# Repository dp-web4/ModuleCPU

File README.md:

# ModuleCPU

**ModBatt Battery Management System - Module Controller**

## Overview

ModuleCPU is the middle-tier controller in ModBatt's hierarchical battery management system, coordinating up to 128 individual CellCPUs while reporting aggregated data to the Pack Controller. It demonstrates how distributed intelligence principles can be applied to embedded battery management at the module scale.

**Implementation Status**: ✅ **Production-ready** - Complete firmware with CAN bus communication, VUART cell management, and hierarchical coordination

### Quick Facts

- **Target Platform**: ATmega64M1 microcontroller (8-bit AVR with CAN)
- **Manages**: Up to 128 CellCPUs via Virtual UART daisy-chain
- **Uplink**: CAN 2.0B bus to Pack Controller (250kbps)
- **Features**: Dual-phase operation, RTC timestamping, robust error handling
- **Role**: Middle management - aggregates cell data, coordinates without micromanaging

## Web4 Ecosystem Context

ModuleCPU can be viewed as a practical demonstration of trust-native architecture patterns applied to embedded battery management:

**Philosophical Framework**: [Synchronism](https://github.com/dp-web4/Synchronism) - Patterns of scale-based coordination and distributed intelligence
**Technical Standard**: [Web4](https://github.com/dp-web4/web4) - Concepts like unforgeable identity and witnessed relationships
**Implementation**: [CellCPU](https://github.com/dp-web4/CellCPU) → **ModuleCPU** (this) → [Pack-Controller](https://github.com/dp-web4/Pack-Controller-EEPROM)

### Design Patterns

ModuleCPU's architecture reflects several patterns that align with Web4 and Synchronism concepts:

- **Identity**: Module serial number framework ready for LCT binding
- **Interface Boundaries**: Well-defined information hiding between layers (CAN upward, VUART downward)
- **Relationship Tracking**: Module maintains awareness of Pack Controller and 94 cells
- **Hierarchical Coordination**: Operates autonomously within constraints from Pack
- **Information Aggregation**: Compresses 188 cell data points into module-level summaries
- **Emergent Intelligence**: System-level balancing from distributed local decisions

See [WEB4_INTEGRATION.md](WEB4_INTEGRATION.md) for how Web4 concepts map to embedded design.
See [SYNCHRONISM_PRINCIPLES.md](SYNCHRONISM_PRINCIPLES.md) for architectural patterns and philosophy.

### Ecosystem Links

- [Synchronism Whitepaper](https://github.com/dp-web4/Synchronism) - Theoretical framework
- [Web4 Standard](https://github.com/dp-web4/web4) - Trust-native architecture concepts
- [ModBatt Web4 Examples](https://github.com/dp-web4/web4/blob/main/docs/modbatt_implementation_examples.md) - Implementation walkthroughs

**This demonstrates how concepts from distributed intelligence theory can inform practical embedded system design.**

---

## Key Features

### 🔋 Cell Management
- **Capacity**: Manages up to 128 CellCPUs in daisy-chain topology
- **Communication**: Virtual UART at 20kbps for cell polling
- **Monitoring**: Aggregates temperature, voltage, and status from all cells
- **Coordination**: Enables balancing, tracks cell health, detects faults

### 📡 Pack Communication
- **Protocol**: CAN 2.0B extended frames with module ID addressing
- **Registration**: Dynamic ID assignment (1-31) from Pack Controller
- **Reporting**: Module-level status, aggregated cell data, error conditions
- **Commands**: State changes, balancing control, time synchronization

### ⚙️ Core Capabilities
- **Dual-Phase Operation**: Separate read/write phases for data integrity
- **RTC Support**: Real-time clock for timestamping
- **Error Handling**: Robust timeout and recovery mechanisms
- **State Management**: OFF/STANDBY/ACTIVE/BALANCE states with safety checks

### 🎯 Performance
- **Memory**: 64KB Flash, 4KB SRAM
- **Response Time**: <50ms for full cell poll cycle (94 cells)
- **CAN Reliability**: Timeout recovery, bus-off handling, error counting
- **Cell Tracking**: Bitmap and statistics for each cell position

## Protocol Synchronization

**Important**: ModuleCPU uses shared CAN protocol definitions maintained in the Pack-Controller-EEPROM repository.

**Authoritative Source**: [Pack-Controller-EEPROM/protocols/](https://github.com/dp-web4/Pack-Controller-EEPROM/tree/main/protocols)
**Local Copy**: `protocols/` (synchronized via `scripts/sync_protocols.sh`)

To update protocols after changes in Pack-Controller:
```bash
./scripts/sync_protocols.sh
# Review changes, test build, commit
```

See `protocols/SYNC_NOTICE.md` for synchronization procedure and versioning.

## System Integration

### ModBatt Architecture

```
Vehicle Control Unit (VCU)
    ↓ CAN Bus
Pack Controller (STM32WB55)
    ↓ CAN Bus (250kbps, extended frames)
ModuleCPU (ATmega64M1) ←─→ 128 × CellCPU (ATtiny45)
    ↓ Virtual UART (20kbps)     ↓
Battery Module             Li-ion Cells
```

### Information Flow

**Upward (Aggregation)**:
```
94 cells × (temp + voltage) = 188 data points
    ↓ (Module aggregates)
Module summary: avg/min/max temps, voltage spread, status bitmap
    ↓ (via CAN)
Pack Controller receives compressed module-level view
```

**Downward (Commands)**:
```
Pack: "Modules enter BALANCE state" (broadcast or targeted)
    ↓ (Module interprets)
Module: Polls cells, coordinates balancing based on voltages
    ↓ (Cells execute)
Cells: Activate balancing FETs based on local decisions
```

## Build Environment

**Important**: This project runs in WSL but uses Windows-based build tools.

- **IDE**: Atmel Studio 7.0+ (Windows)
- **Build**: Must compile in Windows environment
- **WSL**: Used for version control and documentation only
- **Focus**: Code correctness and architecture

See [CLAUDE.md](CLAUDE.md) for development context and recent improvements.

## Recent Enhancements

### Protocol Dependency Resolution (October 2025)
- ✅ Added local `protocols/` directory with sync script
- ✅ Resolved Pack-Controller build dependency
- ✅ ModuleCPU now builds standalone

### CAN Reliability Improvements (September 2025)
- ✅ TX timeout mechanism with backup polling
- ✅ Bus-off recovery with health monitoring
- ✅ Adaptive backoff for persistent errors
- ✅ Diagnostic counters for error tracking

### VUART Edge Detection Fix (September 2025)
- ✅ Rising edge detection for level-shifted signals
- ✅ Improved temperature data reliability
- ✅ Better daisy-chain communication

See [CLAUDE.md](CLAUDE.md) for complete development history and technical details.

## Contributing

See [CONTRIBUTING.md](CONTRIBUTING.md) for development workflow, coding standards, and pull request guidelines.

## License and Patents

### Software License

This software is licensed under the **GNU Affero General Public License v3.0 or later** (AGPL-3.0-or-later).

See [LICENSE](LICENSE) for full license text.
See [LICENSE_SUMMARY.md](LICENSE_SUMMARY.md) for software vs. hardware licensing details.

### Patents

Protected by US Patents:
- **11,469,470**: Hierarchical battery management architecture
- **11,380,942**: Distributed cell controller system
- **11,575,270**: Related pack control systems

**Patent Grant**: Limited patent grant for software use under AGPL-3.0. See [PATENTS.md](PATENTS.md).

**Hardware Licensing**: Separate from software. See `docs/legal/ModBatt_Product_License.pdf`.

### Copyright

© 2023-2025 Modular Battery Technologies, Inc.

**Open Source Release**: October 2025 - Part of the Web4 trust-native ecosystem demonstration.

---

## Related Projects

This repository can be viewed as demonstrating patterns of distributed trust and verifiable provenance in embedded systems.

**Related**: [Web4](https://github.com/dp-web4/web4) (trust architecture) • [Synchronism](https://github.com/dp-web4/Synchronism) (conceptual framing)

---

**Note**: This firmware demonstrates hierarchical coordination patterns in embedded systems. Whether viewed through the lens of Web4/Synchronism concepts or simply as sound battery management architecture, the design patterns are production-tested and functional.

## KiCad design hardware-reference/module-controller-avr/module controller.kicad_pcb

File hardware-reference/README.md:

# ModuleCPU Hardware Reference Designs

**Status**: Reference designs for educational and non-commercial use
**Patent Coverage**: Protected by US Patent 11,469,470 (Hierarchical battery management architecture)
**Last Updated**: October 2025

---

## Overview

This directory contains reference hardware designs for implementing the ModuleCPU concept - a module-level coordinator managing up to 94 autonomous cell controllers. These designs demonstrate one possible hardware implementation of the patented hierarchical battery management architecture.

**Contents**:
- KiCad schematics and PCB layouts
- Bill of Materials (BOM)
- Manufacturing files

---

## Patent Coverage

These hardware designs implement concepts covered by multiple patents in the ModBatt patent portfolio:

### Complete Patent List

**Modular Battery Technologies, Inc. Patent Portfolio**:

1. **US 11,380,942** (PCT/US21/50518) - *High Voltage Battery Module with Series Connected Cells and Internal Relays*
   - Filed: November 2, 2020 | Issued: July 5, 2022
   - Module with series connected cells and relays

2. **US 11,469,470** (PCT/US21/53798) - *Battery Module with Series Connected Cells, Internal Relays and Internal Battery Management System*
   - Filed: January 4, 2021 | Issued: October 11, 2022
   - Cell monitoring/conditioning circuit, PCBAs, methods

3. **US 11,563,241** - *Apparatus and Methods for Removable Battery Module with Internal Relay and Internal Controller*
   - Filed: February 10, 2021 | Issued: December 14, 2022
   - Authentication methods and circuits

4. **US 11,575,270** (PCT/US21/55047) - *Battery Module with Series Connected Cells, Internal Relays and Internal Battery Management System*
   - Filed: February 22, 2021 (CIP) | Issued: February 7, 2023
   - AC coupled comms and methods

5. **US 11,699,817** (PCT/US21/54434) - *Apparatus and Methods for Removable Battery Module with Internal Relay and Internal Controller*
   - Filed: March 31, 2021 | Issued: July 11, 2023
   - System, pack and module controllers, blockchain

6. **US 11,477,027** (PCT/US21/55813) - *Apparatus and Methods for Management of Controlled Objects*
   - Filed: May 11, 2021 | Issued: October 18, 2022
   - Multi-domain management of controlled objects, LCT/blockchain

7. **US 11,936,008** (PCT/US21/60860) - *Electrical Power System with Removable Battery Modules*
   - Filed: November 17, 2021 | Issued: March 19, 2024
   - Dissimilar modules in parallel

8. **US 12,278,913** (PCT/US22/24797) - *Apparatus and Methods for Management of Controlled Objects*
   - Filed: March 31, 2022 | Issued: April 15, 2025
   - Linking of identifiable records

9. **US 11,876,250** (PCT/US22/xxx) - *High Voltage Battery Module with Series Connected Cells and Internal Relays*
   - Filed: May 31, 2022 | Issued: January 16, 2024
   - Dissimilar relays, PLC control bus, linear and PWM modes

10. **US 12,046,722** - *Electrical Power System with Removable Battery Modules*
    - Filed: December 12, 2022 | Issued: July 23, 2024
    - Vehicle and stationary installations having a power system, energizing a bus

11. **US 12,405,309** - *Low Cost Battery Cell Monitoring Circuit*
    - Filed: January 3, 2023 | Issued: September 2, 2025
    - Low cost ASIC

12. **US 12,136,739** - *Low Cost Battery Cell Monitoring Circuit*
    - Filed: December 14, 2023 | Issued: November 5, 2024
    - Low cost ASIC methods

13. **US 12,142,737** - *Electrical Power System with Removable Battery Modules*
    - Filed: December 14, 2023 | Issued: November 12, 2024

14. **US 18/935,265** - *High Voltage Battery Module with 1-Phase and 3-Phase AC Output*
    - Filed: November 1, 2024 | Status: Pending

**Assignee**: Modular Battery Technologies, Inc.
**Inventors**: Dennis Palatov, et al.

### Key Patented Concepts in ModuleCPU Hardware

- Module-level coordination of multiple autonomous cell controllers
- Virtual UART aggregation and CAN bus gateway
- Dual-phase operation for data integrity
- Scale-based hierarchical autonomy with information hiding
- RTC timestamping and coordinated data collection
- High voltage module architecture with internal relays
- Module authentication and blockchain integration
- Dissimilar module operation in parallel configurations
- AC-coupled communication methods

---

## License and Usage Terms

### Software License
The **ModuleCPU firmware** (parent directory) is licensed under **AGPL-3.0-or-later** with a patent grant for software use. See `../LICENSE` for details.

### Hardware Reference Designs
These hardware reference designs are provided under the following terms:

#### ✅ Permitted Uses (Non-Commercial Patent Grant)

You MAY use these designs **without a commercial hardware license** for:

1. **Educational Use**: Academic research, teaching, and learning
2. **Personal/Hobby Use**: Individual projects and experimentation
3. **Research & Development**: Prototyping and testing new concepts
4. **Open Source Development**: Contributing to AGPL-licensed software improvements

**Conditions**:
- No commercial sale or distribution of manufactured hardware
- Acknowledge patent and provide attribution
- Derivative works must include similar non-commercial use notice
- Software modifications must comply with AGPL-3.0-or-later

#### ❌ Restricted Uses (Requires Commercial License)

You MUST obtain a commercial hardware license from Modular Battery Technologies, Inc. for:

1. **Commercial Manufacturing**: Producing hardware for sale
2. **Commercial Products**: Incorporating designs into commercial battery products
3. **Revenue Generation**: Any use where hardware generates revenue directly or indirectly
4. **OEM Integration**: Selling products that include these designs

**Contact**: For commercial licensing inquiries, contact Modular Battery Technologies, Inc.

---

## Technical Scope

These reference designs demonstrate:

- **Module Controller**: ATmega64M1-based coordinator managing up to 128 cells
- **Virtual UART Interface**: Software serial communication to cell controllers (20kbps)
- **CAN Bus Gateway**: Extended CAN 2.0B interface to Pack Controller (500kbps)
- **Dual-Phase Operation**: Coordinated data collection and transmission
- **RTC Integration**: Real-time clock for timestamp synchronization
- **High Voltage Interface**: 300V+ pack voltage monitoring and isolation
- **Relay Control**: Module-level contactor control

**Module Capacity**: Up to 128 cells per module (4096 cells total in 32-module pack)

---

## AS-IS Disclaimer and Limitations

### ⚠️ NO WARRANTY

**THESE HARDWARE REFERENCE DESIGNS ARE PROVIDED "AS IS" WITHOUT WARRANTY OF ANY KIND, EXPRESS OR IMPLIED, INCLUDING BUT NOT LIMITED TO THE WARRANTIES OF MERCHANTABILITY, FITNESS FOR A PARTICULAR PURPOSE, TITLE, AND NON-INFRINGEMENT.**

### Specific Disclaimers

1. **No Guarantee of Functionality**: These designs may contain errors, omissions, or may not function as intended
2. **No Safety Certification**: Designs have NOT been certified for safety (UL, CE, etc.)
3. **Extreme Voltage Hazard**: Module designs operate at **300V+ DC** - **LETHAL VOLTAGE - RISK OF DEATH**
4. **High Power Hazard**: High current capability can cause arc flash, fires, and explosions
5. **Chemical Hazard**: Lithium battery failures can cause fire, toxic fumes, and explosions
6. **No Professional Engineering Review**: Use at your own risk - consult qualified professionals
7. **Rapidly Evolving**: These designs may be outdated or superseded

### 🚨 High Voltage Battery Safety Warning

**DANGER - LETHAL VOLTAGE**: Module-level battery systems operate at 300V+ DC.

- **DEATH or SERIOUS INJURY** can result from contact with high voltage
- **ARC FLASH** hazard - can cause severe burns, blindness, and ignition
- **Stored energy** remains dangerous even after power disconnection
- **Thermal runaway** can cause catastrophic fires and explosions
- **Improper isolation** can energize chassis and cause electrocution

**You are solely responsible for:**
- Proper high voltage safety engineering and interlocks
- Compliance with electrical codes (NEC Article 690, etc.)
- Qualified electrician installation and inspection
- Ground fault and arc fault protection systems
- Emergency disconnect and lockout/tagout procedures
- Fire suppression and containment systems
- Personal protective equipment (PPE) for high voltage work
- Warning labels and access restrictions
- Insurance and liability coverage

**⚠️ WARNING**: Working on high voltage battery systems requires specialized training. Improper work can result in death or serious injury.

---

## Limitation of Liability

**IN NO EVENT SHALL MODULAR BATTERY TECHNOLOGIES, INC., ITS AFFILIATES, OR CONTRIBUTORS BE LIABLE FOR ANY DIRECT, INDIRECT, INCIDENTAL, SPECIAL, EXEMPLARY, OR CONSEQUENTIAL DAMAGES (INCLUDING, BUT NOT LIMITED TO, PROCUREMENT OF SUBSTITUTE GOODS OR SERVICES; LOSS OF USE, DATA, OR PROFITS; BUSINESS INTERRUPTION; PROPERTY DAMAGE; PERSONAL INJURY; OR DEATH) HOWEVER CAUSED AND ON ANY THEORY OF LIABILITY, WHETHER IN CONTRACT, STRICT LIABILITY, OR TORT (INCLUDING NEGLIGENCE OR OTHERWISE) ARISING IN ANY WAY OUT OF THE USE OF THESE DESIGNS, EVEN IF ADVISED OF THE POSSIBILITY OF SUCH DAMAGE.**

---

## Regulatory Compliance

### Your Responsibility

If you manufacture hardware based on these designs, YOU are responsible for:

1. **High Voltage Electrical Safety**:
   - UL/CSA/CE compliance for high voltage battery systems
   - NEC Article 690 (Energy Storage Systems) compliance
   - NFPA 855 (Energy Storage Systems) compliance
   - Arc flash hazard analysis and labeling

2. **FCC/EMC Compliance**:
   - Radio frequency emissions (CAN bus, switching regulators)
   - Immunity to electromagnetic interference

3. **Environmental**:
   - RoHS, REACH, WEEE directives
   - Proper disposal of electronic waste

4. **Transportation**:
   - UN38.3 battery shipping requirements
   - Hazardous materials regulations

5. **Functional Safety**:
   - ISO 26262 (if automotive)
   - IEC 61508 (industrial safety)
   - FMEA and safety analysis

6. **Local Codes**:
   - Electrical codes and building codes in your jurisdiction
   - Fire marshal approval for energy storage installations

### No Compliance Warranty

**These designs have NOT been tested for regulatory compliance.** You must perform your own testing and certification.

---

## Design Files Information

### KiCad Version
Designs created with KiCad EDA (exact version in `.kicad_pro` files)

### File Structure
- `.kicad_sch` - Schematic files (hierarchical sheets: MC, HV PWR)
- `.kicad_pcb` - PCB layout files
- `.csv` / `.ods` / `.pdf` - Bill of Materials (multiple variants)
- `mfg/` - Manufacturing output files (Gerbers, drill files, pick-and-place)
- `.step` - 3D mechanical models for enclosure integration

### Viewing and Editing
1. Download and install KiCad: https://www.kicad.org/
2. Open `module controller.kicad_pro` project file
3. Libraries may need to be remapped on first open
4. Review hierarchical sheets: MC (main controller), HV PWR (high voltage power)

---

## Attribution and Derivative Works

If you create derivative works based on these designs:

1. **Acknowledge the Source**:
   ```
   Based on ModuleCPU hardware reference designs
   Copyright (c) 2024-2025 Modular Battery Technologies, Inc.
   https://github.com/dp-web4/ModuleCPU
   ```

2. **Maintain Patent Notice**: Include reference to ModBatt patent portfolio (see Patent Coverage section)

3. **Propagate Non-Commercial Terms**: If distributing derivatives, include similar non-commercial use restrictions

4. **Maintain Safety Warnings**: High voltage warnings must be prominently displayed

5. **No Endorsement**: Do not imply that your derivative work is endorsed by Modular Battery Technologies, Inc.

---

## Support and Contributions

### No Support Commitment
These reference designs are provided without support. No assistance is guaranteed.

### Community Contributions
Improvements to these reference designs are welcome via pull requests:
- Clearly document changes and reasoning
- **CRITICAL**: Maintain safety-critical design margins for high voltage isolation
- Include high voltage safety review and analysis
- Include SPDX license headers if adding new files
- Sign-off on contributions (Developer Certificate of Origin)

**Safety-Critical Elements** (require extra scrutiny):
- High voltage isolation and creepage distances
- Relay driver circuits and flyback protection
- CAN bus termination and isolation
- Power supply regulation and protection
- Ground fault detection circuitry

---

## Relationship to Software License

**Key Distinction**:
- **Software (ModuleCPU firmware)**: AGPL-3.0-or-later with broad patent grant for software use
- **Hardware (these designs)**: Non-commercial patent grant only; commercial use requires separate license

**Why the Difference?**
- Software improvements benefit the ecosystem when shared (AGPL ensures sharing)
- Hardware manufacturing involves significant capital investment, safety liability, and certification costs
- Patent coverage primarily relates to hardware architecture and hierarchical topology

**Can I modify the software for use on different hardware?**
- Yes! The AGPL-3.0 software license and patent grant apply to the software
- You can run modified ModuleCPU software on your own hardware implementations
- Commercial hardware sales still require a hardware patent license

---

## Integration with CellCPU

ModuleCPU hardware is designed to work with CellCPU cell controllers:
- **CellCPU**: https://github.com/dp-web4/CellCPU
- **Communication**: Virtual UART at 20kbps
- **Topology**: Daisy-chain of up to 94 cells per module

Both CellCPU and ModuleCPU reference designs follow the same licensing model.

---

## Questions?

**Technical Questions**: Open an issue on GitHub (https://github.com/dp-web4/ModuleCPU/issues)
**Commercial Licensing**: Contact Modular Battery Technologies, Inc.
**Safety Concerns**: Consult a qualified electrical engineer experienced in high voltage battery systems

---

## Legal Summary

| **Aspect** | **Terms** |
|------------|-----------|
| **Software License** | AGPL-3.0-or-later (see `../LICENSE`) |
| **Hardware Designs** | Reference only - non-commercial patent grant |
| **Patents** | 14 US patents (1 pending) - commercial use requires license |
| **Warranty** | NONE - "AS IS" |
| **Liability** | User assumes all risk and liability |
| **Safety** | NOT certified - **LETHAL HIGH VOLTAGE** battery application |
| **Commercial Use** | Requires separate commercial license agreement |

---

**© 2024-2025 Modular Battery Technologies, Inc.**
**Patents**: 14 US patents covering battery management systems (see Patent Coverage section)
**Reference designs provided for educational and non-commercial use only**

---

**⚠️ FINAL WARNING**: These designs involve lethal voltages and high energy battery systems. Death or serious injury can result from improper use. Only qualified professionals should work with high voltage battery systems. You use these designs entirely at your own risk.

---

*Last updated: October 2025*
*For latest terms, see https://github.com/dp-web4/ModuleCPU*

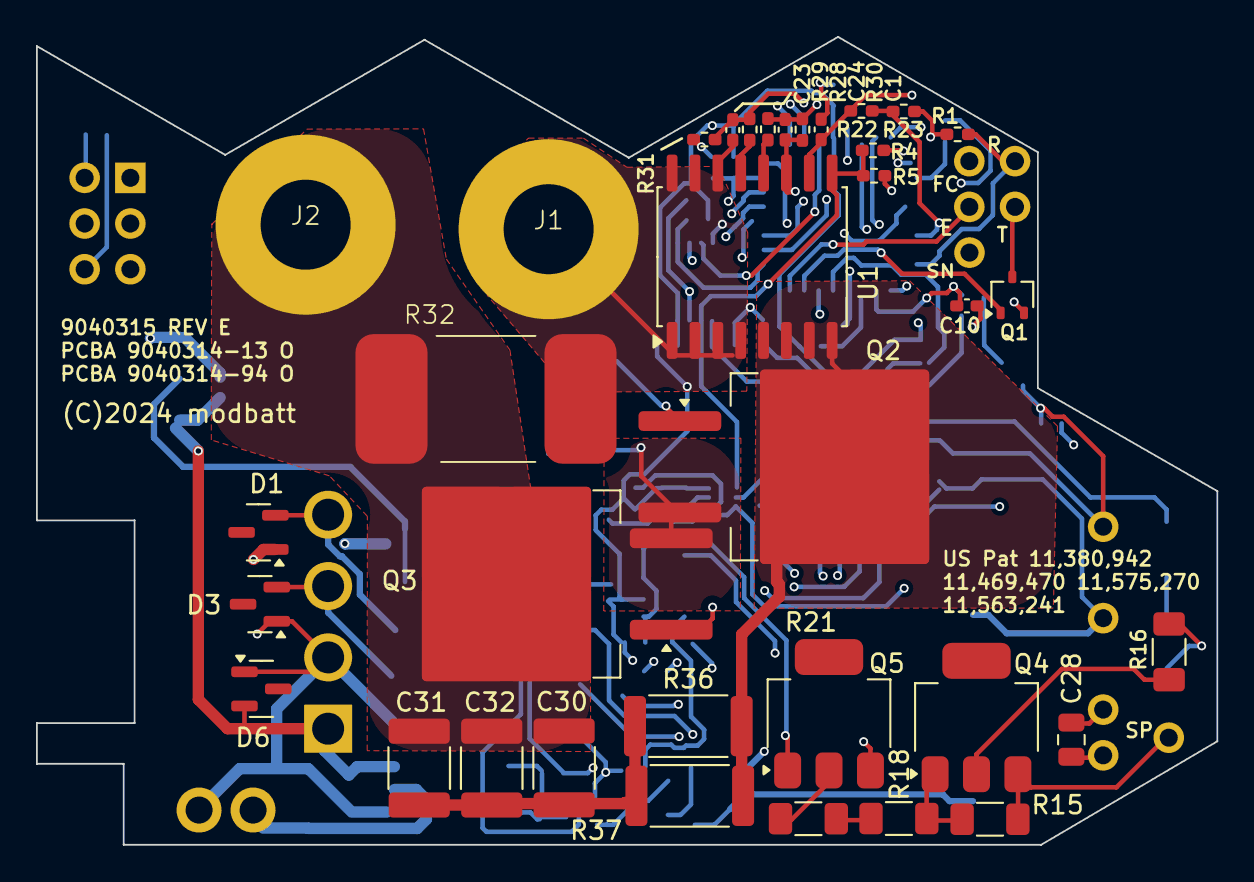
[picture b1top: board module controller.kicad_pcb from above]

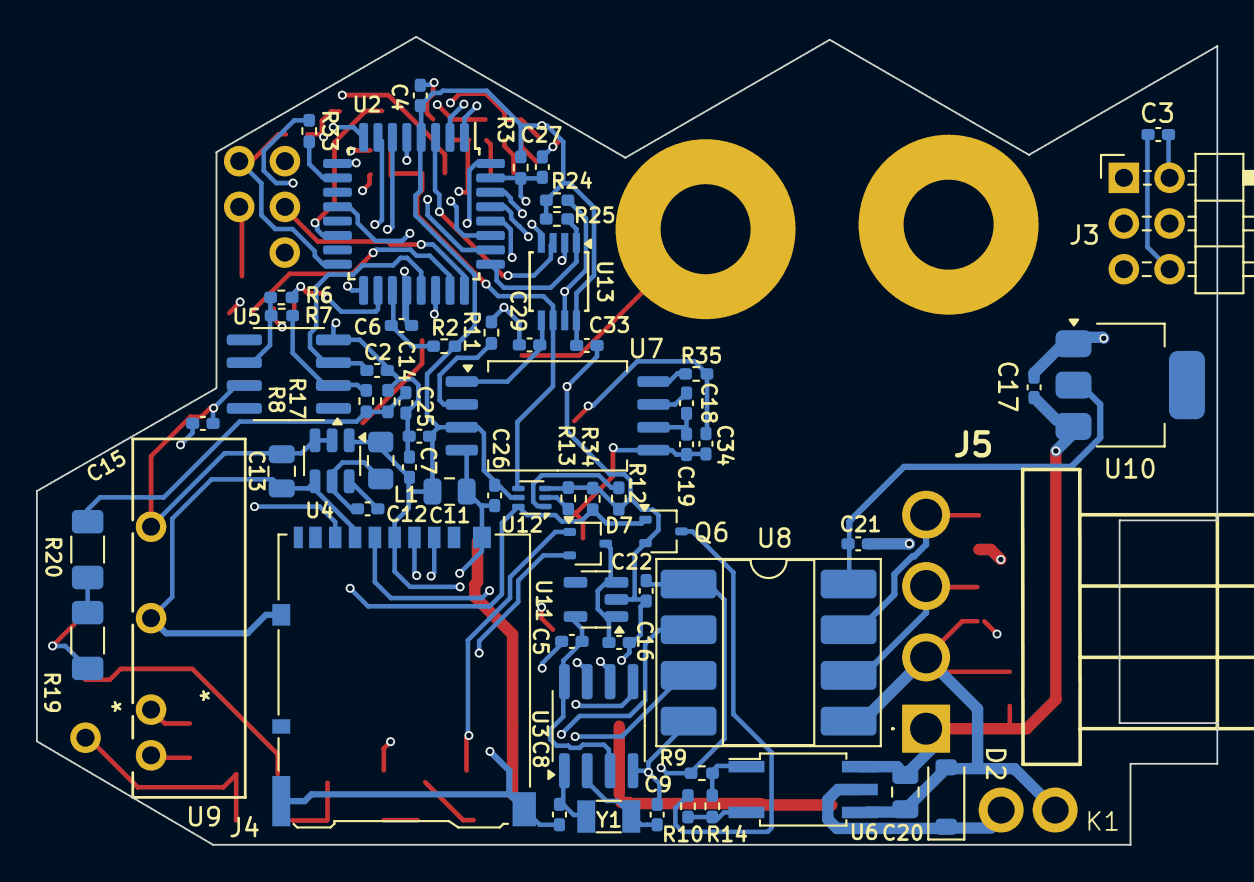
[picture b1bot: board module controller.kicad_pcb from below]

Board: 4 copper layers, 65.6 x 44.9 mm, 107 parts (65 on the bottom side), 73 nets.

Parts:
C1: 2.2uF; C_0402_1005Metric_Pad0.74x0.62mm_HandSolder
C2: 10nF; C_0402_1005Metric_Pad0.74x0.62mm_HandSolder
C3, C4, C5, C6, C7, C12, C15, C25, C26, C27, C29, C33: .1uF; C_0402_1005Metric_Pad0.74x0.62mm_HandSolder
C8, C9: 7pF; C_0402_1005Metric_Pad0.74x0.62mm_HandSolder
C10, C14, C23, C24, C34: 10pF; C_0402_1005Metric_Pad0.74x0.62mm_HandSolder
C11, C13, C20, C28: 22uF 25V; C_0805_2012Metric
C16, C18, C19: 1uF; C_0402_1005Metric_Pad0.74x0.62mm_HandSolder
C17, C21, C22: .1uF 50V; C_0402_1005Metric_Pad0.74x0.62mm_HandSolder
C30, C31, C32: .1uF 1KV; C_1812_4532Metric
D1, D3, D6: MMBZ27VCLT1G; SOT-23
D2: 20V 350mA SOD123; D_SOD-123
D7: BAT54CW; SOT-323_SC-70
J1, J2: TERM; TERMINAL
J3: Debug; PinHeader_2x03_P2.54mm_Horizontal
J4: Micro_SD_Card_Det_Hirose_DM3AT; microSD_HC_Hirose_DM3AT-SF-PEJM5
J5: 640389-4; 6403896-4
J6, J7, J8, J9, J10, J11: Conn_01x01_Pin; PinHeader_1x01_P1.00mm_Horizontal
K1: DVR05; modbatt relay tab
L1: 4.7uH; L_0805_2012Metric_Pad1.15x1.40mm_HandSolder
Q1, Q6: 2N7002; SOT-323_SC-70
Q2, Q3: IPB60R040CFD7ATMA1; TO-263-3_TabPin2
Q4: ZVP0545G; SOT-223
Q5: ZVN0545G; SOT-223
R1: 1K; R_0402_1005Metric_Pad0.72x0.64mm_HandSolder
R2: 4.7 OHM; R_0402_1005Metric_Pad0.72x0.64mm_HandSolder
R3, R4, R24, R25, R33: 4.7K; R_0402_1005Metric_Pad0.72x0.64mm_HandSolder
R5, R22, R23, R34: 100K; R_0402_1005Metric_Pad0.72x0.64mm_HandSolder
R6: 10K; R_0402_1005Metric_Pad0.72x0.64mm_HandSolder
R7, R8: 1.0M 0.1%; R_0402_1005Metric_Pad0.72x0.64mm_HandSolder
R9, R10: 68; R_0402_1005Metric_Pad0.72x0.64mm_HandSolder
R11: 200K; R_0402_1005Metric_Pad0.72x0.64mm_HandSolder
R12, R13: 787K 1%; R_0402_1005Metric_Pad0.72x0.64mm_HandSolder
R14, R28, R29, R30, R31: 4.99K 0.1%; R_0402_1005Metric_Pad0.72x0.64mm_HandSolder
R15: 200K 1206; R_1206_3216Metric_Pad1.30x1.75mm_HandSolder
R16, R19, R20: 2.7M 0.1% 1206; R_1206_3216Metric_Pad1.30x1.75mm_HandSolder
R17: 100K 0.1%; R_0402_1005Metric_Pad0.72x0.64mm_HandSolder
R18, R21: 2.7M; R_1206_3216Metric_Pad1.30x1.75mm_HandSolder
R32: 33K 3560 6W; 3560
R35: 22; R_0402_1005Metric_Pad0.72x0.64mm_HandSolder
R36, R37: 4R0 500V; R_2512_6332Metric
U1: ACS37002LMABTR-050B5; SOIC-16W_7.5x10.3mm_P1.27mm
U2: ATmega64M1-AU; TQFP-32_7x7mm_P0.8mm
U3: MCP7940N-xMS; SOIC-8_3.9x4.9mm_P1.27mm
U4: AP63203WU; TSOT-23-6
U5: TLV333 8SOIC; SOIC-8_3.9x4.9mm_P1.27mm
U6: TLP152; SO-6_4.4x3.6mm_P1.27mm
U7: TPSI3050D; SOIC-8_7.5x5.85mm_P1.27mm
U8: ISO1050DUB; DIP-8_W8.89mm_SMDSocket_LongPads
U9: IB1205LS-1WR3; SIP6_IB_LS-1WR3_MNS
U10: AZ1117-5.0; SOT-223
U11: MIC5504-3.3YM5; SOT-23-5
U12: TMP392; SOT-563
U13: TC7WH74FU; TSSOP-8_3x3mm_P0.65mm
Y1: 32.768KHz SC-32; Crystal_SMD_3215-2Pin_3.2x1.5mm

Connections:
/12V+: C17.1, C20.1, C28.1, D6.2 (K), J5.1, U6.6 (VCC), U9.1 (VIN), U10.3 (VI)
/12V-: C17.2, C20.2, C21.2, C28.2, D1.1 (K), D2.2 (A), D3.1 (K), D6.1 (K), J5.2, K1.3, U6.4 (VEE), U8.5 (GND2), U9.2 (GND), U10.1 (GND)
/CAN H: D1.2 (K), J5.4, U8.7 (CANH)
/CAN L: D3.2 (K), J5.3, U8.6 (CANL)
/CELL EN: J6.1, U2.24 (PB4)
/CSOUT: Q2.2 (D), R36.2, R37.2, U1.5 (IP-), U1.6 (IP-), U1.7 (IP-), U1.8 (IP-)
/FIRST CELL: D7.2, J11.1
/HV PWR/5V: C1.1, C13.1, C15.1, D7.1, Q5.1 (G), R22.1, U1.10 (VCC), U4.2 (EN), U4.3 (IN), U5.7 (V+), U9.6 (+VO)
/HV PWR/ADC REF 2.56V: C2.1, U2.21 (AREF/ISRC), U5.3 (+)
/HV PWR/CAN RXD: U2.7 (RXCAN/PC3), U8.2 (RXD)
/HV PWR/CAN TXD: U2.6 (TXCAN/PC2), U8.3 (TXD)
/HV PWR/DIVIDER: C14.1, R8.2, R17.2, R20.1
/HV PWR/FET EN: C29.1, U7.1 (EN), U13.5 (Q)
/HV PWR/FET G: C34.1, Q2.1 (G), Q3.1 (G), R35.2
/HV PWR/FET S: C19.2, C34.2, Q2.3 (S), Q3.3 (S), U7.5 (VSSS)
/HV PWR/MC PWR: C3.1, C4.1, C7.1, C11.1, C22.1, C25.2, C26.1, C33.1, J3.2, J4.4 (VDD), L1.1, R2.1, R3.1, R9.2, R24.1, R25.1, U2.4 (VCC), U4.1 (FB), U7.3 (VDDP), U8.1 (VCC1), U12.5 (VDD), U13.8 (VCC)
/HV PWR/RELAY EN: R33.1, U2.10 (PWM/XTAL1/PE1)
/HV PWR/RELAY POS: D2.1 (K), K1.2, U6.5 (VO)
/HV PWR/STRING V SENSE: C10.1, R6.1, U2.18 (ADC9/PC5)
/HV PWR/~OCF: R4.2, R5.1, U1.9 (-OCF), U12.4 (OUTB), U13.6 (~CLR)
/MC RX: J7.1, R1.1, U2.16 (INT1/ADC5/PB2)
/MC TX: J8.1, Q1.3 (D)
/MODULE CONTROLLER/5V DET: R22.2, R23.1, U2.14 (INT0/ADC3/PD6)
/MODULE CONTROLLER/CURRENT ADC0: R28.2, U1.12 (VIOUT)
/MODULE CONTROLLER/CURRENT ADC1: R29.2, U1.13 (VREF)
/MODULE CONTROLLER/MC TX: Q1.1 (G), U2.23 (PB3)
/MODULE CONTROLLER/NV VCC: C5.1, U3.3 (VBAT), U3.8 (VCC), U11.5 (VOUT)
/TERM NEG: C30.2, C31.2, C32.2, J2.1, Q3.2 (D), R32.1
unnamed: C30.1, C31.1, C32.1, R36.1, R37.1
unnamed: J3.1, U2.1 (MISO_A/PD2)
unnamed: J3.3, U2.12 (ADC1/RXD/SCK_A/PD4)
unnamed: J3.4, U2.2 (TXD/MOSI_A/PD3)
unnamed: C27.1, J3.5, R3.2, U2.31 (~RESET/PE0)
unnamed: J4.5 (CLK), U2.28 (SCK/ADC4/PB7)
unnamed: J4.3 (CMD), U2.9 (PB1)
unnamed: J4.7 (DAT0), U2.8 (PB0)
unnamed: J4.2 (DAT3/CD), U2.22 (ADC10/PC6)
unnamed: Q4.2 (D), R16.2
unnamed: Q4.1 (G), R15.2, R18.1
unnamed: Q5.2 (D), R21.2
unnamed: Q6.3 (D), R10.1
unnamed: Q6.1 (G), R33.2, R34.1, U12.6 (OUTA)
unnamed: R6.2, R7.1, U5.6
unnamed: R16.1, R19.2
unnamed: R18.2, R21.1
unnamed: R19.1, R20.2
unnamed: C23.1, R29.1, R31.2, U2.27 (ADC7/PB6)
unnamed: R4.1, U2.17 (ADC8/PC4)
unnamed: C6.1, R2.2, U2.19 (AVCC)
unnamed: C24.1, R28.1, R30.2, U2.26 (INT2/ADC6/PB5)
unnamed: U2.30 (INT3/PC0), U3.7 (MFP)
unnamed: U2.29 (PD0), U3.6 (SCL)
unnamed: U2.32 (PD1), U3.5 (SDA)
unnamed: C8.2, U3.1 (X1), Y1.2
unnamed: C9.2, U3.2 (X2), Y1.1
unnamed: C12.1, U4.6 (BST)
unnamed: C12.2, L1.2, U4.5 (SW)
unnamed: R7.2, R8.1, U5.2 (-)
unnamed: R9.1, R14.1, U6.1 (A)
unnamed: R10.2, R14.2, U6.3 (C)
unnamed: R11.2, U7.2 (PXFR)
unnamed: C18.1, U7.7 (VDDH)
unnamed: C18.2, C19.1, U7.6 (VDDM)
unnamed: R35.1, U7.8 (VDRV)
unnamed: C21.1, U8.8 (VCC2), U10.2 (VO)
unnamed: C16.1, D7.3, U11.1 (VIN), U11.3 (EN)
unnamed: R12.2, U12.1 (SETA)
unnamed: R13.2, U12.2 (SETB)
unnamed: R25.2, U2.25 (PC7), U13.1 (C)
unnamed: R24.2, U13.2 (D), U13.7 (~PR)
unnamed: U2.3 (PC1), U13.3 (~Q)
STRING NEG: C1.2, C2.2, C3.2, C4.2, C5.2, C6.2, C7.2, C8.1, C9.1, C10.2, C11.2, C13.2, C14.2, C15.2, C16.2, C22.2, C23.2, C24.2, C25.1, C26.2, C27.2, C29.2, C33.2, J1.1, J3.6, J4.6 (VSS), J4.11 (SHIELD), J10.1, Q1.2 (S), Q5.3 (S), Q6.2 (S), R1.2, R5.2, R11.1, R12.1, R13.1, R17.1, R23.2, R30.1, R31.1, R32.2, R34.2, U1.1 (IP+), U1.2 (IP+), U1.3 (IP+), U1.4 (IP+), U1.11 (VOC), U1.14 (GS1), U1.15 (GND), U1.16 (GS0), U2.5 (GND), U2.20 (AGND), U3.4 (VSS), U4.4 (GND), U5.4 (V-), U7.4 (VSSP), U8.4 (GND1), U9.4 (0V), U11.2 (GND), U12.3 (GND), U13.4 (GND)
STRING POS: J9.1, Q4.3 (S), R15.1

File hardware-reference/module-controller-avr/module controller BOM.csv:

"#","Reference","Qty","Manufacturer_Name","Manufacturer_Part_Number","Description","Value","Footprint","MB P/N","Exclude from BOM"
"1","C1","1","","","","2.2uF","Capacitor_SMD:C_0402_1005Metric_Pad0.74x0.62mm_HandSolder","",""
"2","C2","1","","","","10nF","Capacitor_SMD:C_0402_1005Metric_Pad0.74x0.62mm_HandSolder","",""
"3","C10,C14,C23,C24,C34","5","","","","10pF","Capacitor_SMD:C_0402_1005Metric_Pad0.74x0.62mm_HandSolder","",""
"4","C11,C13,C20,C28","4","","","","22uF  25V","Capacitor_SMD:C_0805_2012Metric","",""
"5","C16,C18,C19","3","","","","1uF","Capacitor_SMD:C_0402_1005Metric_Pad0.74x0.62mm_HandSolder","",""
"6","C17,C21,C22","3","","","",".1uF 50V","Capacitor_SMD:C_0402_1005Metric_Pad0.74x0.62mm_HandSolder","",""
"7","C3,C4,C5,C6,C7,C12,C15,C25,C26,C27,C29,C33","12","","","",".1uF","Capacitor_SMD:C_0402_1005Metric_Pad0.74x0.62mm_HandSolder","",""
"8","C30,C31,C32","3","","","",".1uF 1KV","Capacitor_SMD:C_1812_4532Metric","",""
"9","C8,C9","2","","","","7pF","Capacitor_SMD:C_0402_1005Metric_Pad0.74x0.62mm_HandSolder","",""
"10","D2","1","","","","20V 350mA SOD123","Diode_SMD:D_SOD-123","",""
"11","D7","1","","","Dual schottky barrier diode, common cathode, SOT-323","BAT54CW","Package_TO_SOT_SMD:SOT-323_SC-70","",""
"12","D1,D3,D6","3","","","","MMBZ27VCLT1G","modbatt footprints:SOT-23","",""
"13","J3","1","","","","Debug","Connector_PinHeader_2.54mm:PinHeader_2x03_P2.54mm_Horizontal","",""
"14","J4","1","","","","Micro_SD_Card_Det_Hirose_DM3AT","modbatt footprints:microSD_HC_Hirose_DM3AT-SF-PEJM5","",""
"15","J5","1","TE Connectivity","640389-6","","640389-4","modbatt footprints:6403896-4","",""
"16","J1,J2","2","","","","TERM","modbatt footprints:TERMINAL","",""
"17","J6,J7,J8,J9,J10,J11","6","","","","Conn_01x01_Pin","modbatt footprints:PinHeader_1x01_P1.00mm_Horizontal","",""
"18","K1","1","","","","DVR05","modbatt footprints:modbatt relay tab","",""
"19","L1","1","","","","4.7uH","Inductor_SMD:L_0805_2012Metric_Pad1.15x1.40mm_HandSolder","",""
"20","Q4","1","","","","ZVP0545G","Package_TO_SOT_SMD:SOT-223","",""
"21","Q5","1","","","","ZVN0545G","Package_TO_SOT_SMD:SOT-223","",""
"22","Q1,Q6","2","","","","2N7002","Package_TO_SOT_SMD:SOT-323_SC-70","",""
"23","Q2,Q3","2","INFINEON","IPB60R040CFD7ATMA1","MOSFET, N-CH, 600V, 50A, 150DEG C, 227W","MOSFET 600V","modbatt footprints:TO-263-3_TabPin2","",""
"24","R1","1","YAGEO","RT0402FRE101KL","RES 0402 1K OHM 1/16W 1%","1KΩ","Resistor_SMD:R_0402_1005Metric_Pad0.72x0.64mm_HandSolder","9042161",""
"25","R2","1","TE Connectivity","CRGCQ0402J4R7","RES 0402 4.7OHM 1/16W 5%","4.7Ω","Resistor_SMD:R_0402_1005Metric_Pad0.72x0.64mm_HandSolder","9042031",""
"26","R6","1","YAGEO","RC0402JR-0710KL","RES 0402 10K OHM 1/16W 5%","10KΩ","Resistor_SMD:R_0402_1005Metric_Pad0.72x0.64mm_HandSolder","9042011",""
"27","R11","1","YAGEO","RC0402JR-13200KL","RES 0402 200K OHM 1/16W 5%","200KΩ","Resistor_SMD:R_0402_1005Metric_Pad0.72x0.64mm_HandSolder","9042113",""
"28","R15","1","YAGEO ","RC1206JR-07200KL ","RES 1206 200k Ohms 1/4W 5%","200KΩ","Resistor_SMD:R_1206_3216Metric_Pad1.30x1.75mm_HandSolder","9042111",""
"29","R17","1","YAGEO","RT0402BRE07100KL","RES 100K Ohm 0.1% 1/16W 50V 50ppm","100KΩ 0.1%","Resistor_SMD:R_0402_1005Metric_Pad0.72x0.64mm_HandSolder","9042090",""
"30","R32","1","TE Connectivity","356033KFT","RES 3560 33K 6W 1%","33KΩ","modbatt footprints:3560","9042127",""
"31","R35","1","PANASONIC","ERJ-U02J220X","RES 0402 22 OHM 5%","22Ω","Resistor_SMD:R_0402_1005Metric_Pad0.72x0.64mm_HandSolder","9042149",""
"32","R12,R13","2","Vishay","CRCW0402787KFKED","RES 0402 787KOHM 1% 1/16W","787KΩ 1%","Resistor_SMD:R_0402_1005Metric_Pad0.72x0.64mm_HandSolder","9042160",""
"33","R14,R28,R29,R30,R31","5","YAGEO ","RT0402BRE074K99L","RES 0402 4.99KOHM 0.1% 1/16W","4.99KΩ 0.1%","Resistor_SMD:R_0402_1005Metric_Pad0.72x0.64mm_HandSolder","9042081",""
"34","R16,R18,R19,R20,R21","5","SUSUMU,Susumu","RG3216P-2704-B-T1","RES 1206 2.7M OHM 0.1% 1/4W","2.7MΩ  0.1%","Resistor_SMD:R_1206_3216Metric_Pad1.30x1.75mm_HandSolder","9042061",""
"35","R3,R4,R24,R25,R33","5","YAGEO","AC0402FR-134K7L ","RES 0402 4.7K OHM 62.5mW 1%","4.7KΩ","Resistor_SMD:R_0402_1005Metric_Pad0.72x0.64mm_HandSolder","9042110",""
"36","R36,R37","2","VISHAY","CRCW25126R04FKEGHP","RES 6.04 OHM 1.5W 1% 2512","6.04Ω","Resistor_SMD:R_2512_6332Metric","9042155",""
"37","R5,R22,R23,R34","4","TE Connectivity","CRG0402J100K/10","RES 0402 100K OHM 1/16W 5%","100KΩ","Resistor_SMD:R_0402_1005Metric_Pad0.72x0.64mm_HandSolder","9042003",""
"38","R7,R8","2","YAGEO","RE0402BRE071ML","RES 0402 1M OHM 1/16W 0.1%","1.0MΩ 0.1%","Resistor_SMD:R_0402_1005Metric_Pad0.72x0.64mm_HandSolder","9042012",""
"39","R9,R10","2","Walsin","WR04X68R0FTL","RES 0402 68 OHM 1% 1/16W","68Ω","Resistor_SMD:R_0402_1005Metric_Pad0.72x0.64mm_HandSolder","9042095",""
"40","U1","1","Allegro MicroSystems ","ACS37002LMABTR-050B5","Board Mount Current Sensors 400KHZ","ACS37002LMABTR-050B5","Package_SO:SOIC-16W_7.5x10.3mm_P1.27mm","9042071",""
"41","U2","1","  Microchip Technology","ATmega64M1-AU","8-bit Microcontrollers - MCU 16 MHz, 85DEG","ATmega64M1-AU","modbatt footprints:TQFP-32_7x7mm_P0.8mm","9042027",""
"42","U3","1","Microchip Technology ","MCP7940NT-I/SN ","Real Time Clock I2C GP RTCC 64B SRAM","MCP7940N","Package_SO:SOIC-8_3.9x4.9mm_P1.27mm","9042023",""
"43","U4","1","Diodes Incorporated","AP63203WU-7","IC REG BUCK 3.3V 2A TSOT26","AP63203WU","Package_TO_SOT_SMD:TSOT-23-6","9042036*",""
"44","U5","1","Texas Instruments","TLV333IDR ","Op Amps Single 350-kHz low -noise RRIO CMOS","TLV333 8SOIC","Package_SO:SOIC-8_3.9x4.9mm_P1.27mm","9042089",""
"45","U6","1","TOSHIBA  ","TLP152(TPL,E","Optically Isolated Gate Drivers Gate Drive Phcplr 3750 Vrms","TLP152","modbatt footprints:SO-6_4.4x3.6mm_P1.27mm","9042076",""
"46","U7","1","Texas Instruments","TPSI3050DWZR ","Galvanically Isolated Gate Drivers Isolated switch driver","TPSI3050D","Package_SO:SOIC-8_7.5x5.85mm_P1.27mm","9042157",""
"47","U8","1","Texas Instruments","ISO1050DUB","Digital Isolators Iso 5V CAN Xcvr","ISO1050DUB","modbatt footprints:DIP-8_W8.89mm_SMDSocket_LongPads","9042022",""
"48","U9","1","MORNSUN","IB 1205LS-1WR3","Isolated Module DC DC Converter 1 Output 5V 200mA 11.4V - 12.6V Input","DC-DC SIP6","modbatt footprints:SIP6_IB_LS-1WR3_MNS","9042056",""
"49","U10","1","Diodes Incorporated","AZ1117IH-5.0TRG1","Voltage Regulators LDO BJT HiCurr 1.35A 10Hz to 10KHz","AZ1117-5.0","Package_TO_SOT_SMD:SOT-223","9042057*",""
"50","U11","1","Microchip Technology","MIC5504-3.3YM5","LDO Voltage Regulators Single 300mA","MIC5504-3.3YM5","Package_TO_SOT_SMD:SOT-23-5","9042100",""
"51","U12","1","Texas Instruments ","TMP392A2DRLR","Board Mount Temperature Sensors TMP392 Dual-channel","TMP392","modbatt footprints:SOT-563","9042133",""
"52","U13","1","TOSHIBA","TC7WH74FU","Flip Flops L-MOS LOGIC (VHS)","TC7WH74FU","Package_SO:TSSOP-8_3x3mm_P0.65mm","9042143",""
"53","Y1","1","Seiko Semiconductors ","SC32S-7PF20PPM","Crystals 32.768kHz 7pF +/-20PPM","32.768KHz SC-32","Crystal:Crystal_SMD_3215-2Pin_3.2x1.5mm","9042006",""

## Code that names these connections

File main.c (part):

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#define TIMER1_CHA_INT(x)					TIFR1 = (1 << OCF1A); OCR1A = (uint16_t) (TCNT1 + (x)); TIMSK1 |= (1 << OCIE1A)

#define PIN_RELAY_EN						(PORTE1)  //moved from c0!
#define PIN_OCF_N							(PORTC1)  // when FET is on configure as input to monitor OCF, value is inverted starting 
#define PIN_FET_EN							(PORTC4)  // set high to enable clocking of FET, set low to asynchronously disable FET
#define PIN_FET_CK							(PORTC7)  // cycle low then high (no delay needed) to clock FET to ON.  if FET_EN is low this will have no effect.

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
// prior to rev E.  
//#define FET_EN_CONFIGURE()					PORTC &= ~  (((uint8_t) (1 << PIN_FET_EN)) | ((uint8_t) (1 << PIN_OCF_N))); DDRC |= (((uint8_t) (1 << PIN_FET_EN)) | ((uint8_t) (1 << PIN_OCF_N)) ); // set both as outputs and OFF
//#define FET_EN_ASSERT()						DDRC &= ~ ((uint8_t) (1 << PIN_OCF_N));  PORTC |= ((uint8_t) (1 << PIN_FET_EN));  // set to read OCF and drive FET_EN
//#define FET_EN_DEASSERT()					PORTC &= ~  (((uint8_t) (1 << PIN_FET_EN)) | ((uint8_t) (1 << PIN_OCF_N))); DDRC |= (((uint8_t) (1 << PIN_FET_EN)) | ((uint8_t) (1 << PIN_OCF_N)) ); // set both as outputs and OFF
//#define FET_ASSERTED()						(PINC & ((uint8_t) (1 << PIN_FET_EN)))

// starting with rev E
// initial configuration  PC4 low (external pulldown), PC7 high (it is also pulled up externally), PC1 input
// to enable FET to be turned on set PC4 high.  this removes the asynchronous /CLR from the flipflop.  note that an over temp or over current condition will override this
// to turn FET on once it is enabled, cycle the clock by driving PC7 low then high.  no need for delay inbetween.
// to turn FET off when it's on, drive PC4 low.  this will asynchronously clear the flipflop
// read the status of FET EN on PC1 (inverted!)
// an overtemp or overcurrent will drive /CLR and cause PC1 to go high, so a rising edge interrupt can be used to detect these events

#define FET_EN_CONFIGURE()					PORTC &= ~  ((uint8_t) (1 << PIN_FET_EN)); DDRC |= ((uint8_t) (1 << PIN_FET_EN)); DDRC &= ~ ((uint8_t) (1 << PIN_OCF_N)); DDRC |= ((uint8_t) (1 << PIN_FET_CK)) // set FET_EN as output and low, OCF_N as input, FET_CK as output
#define FET_EN_ASSERT()						PORTC |= ((uint8_t) (1 << PIN_FET_EN)); PORTC &= ~ ((uint8_t) (1 << PIN_FET_CK)); PORTC |= ((uint8_t) (1 << PIN_FET_CK))  // set  FET_EN high, then drive flipflop clock low then high
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				
				WDTSetLeash(WDT_LEASH_LONG,EWDT_NORMAL);

				// Disable pin change interrupt for /OCF (and bank C)
				PCMSK1 &= (uint8_t) ~(1 << PIN_OCF_N);		// /OCF interrupt disable
				PCICR &= (uint8_t) ~(1 << PCIE1);			// Bank C interrupt disable
				
				sg_bCellBalanceReady = true;
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	
				WDTSetLeash(WDT_LEASH_SHORT,EWDT_MECH_RLY_ON);
				
				// Disable pin change interrupt for /OCF (and bank C)
				PCMSK1 &= (uint8_t) ~(1 << PIN_OCF_N);		// /OCF interrupt disable
				PCICR &= (uint8_t) ~(1 << PCIE1);			// Bank C interrupt disable

				// Turn on the relay (does nothing when transiting to off)
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				sg_bCellBalancedOnce = false;
				sg_bStopDischarge = true;

				// Enable pin change interrupt for /OCF (and bank C)
				PCMSK1 |= (1 << PIN_OCF_N);		// /OCF interrupt enable
				PCICR |= (1 << PCIE1);			// Bank C interrupt enable


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				ModuleControllerStateSet( EMODSTATE_STANDBY );
				}
		
			// Disable pin change interrupt for /OCF (and bank C)
			PCMSK1 &= (uint8_t) ~(1 << PIN_OCF_N);		// /OCF interrupt disable
			PCICR &= (uint8_t) ~(1 << PCIE1);			// Bank C interrupt disable
	

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				

// CURRENT0 and CURRENT1 current measurements combine to form a current value
// current ADC0 (PB5, vout on current sensor) - this is the current reading.  it is used in conjunction with ADC1
// current ADC1 (PB6, vref on current sensor) - this reading is the zero-current value.  subtract it from ADC0 to get a signed current value.
static void ModuleCurrentConvertReadings( void )
{
	int16_t s16Offset;
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		PORT_5V_DET |= (1 << PIN_5V_DET);

		// Ensure SPI is routed to Port B (not Port D) - clear SPIPS bit
		// This prevents SPI peripheral from interfering with PD2/PD3/PD4
		MCUCR &= (uint8_t) ~(1 << SPIPS);

		// Enable pullups on debug/SPI pins (PD2=MISO, PD3=MOSI, PD4=SCK in alternate mode)
		// Prevents floating inputs from triggering spurious interrupts when debug cable disconnected
		DDRD &= (uint8_t) ~((1 << PORTD2) | (1 << PORTD3) | (1 << PORTD4));  // Ensure inputs
		PORTD |= (1 << PORTD2) | (1 << PORTD3) | (1 << PORTD4);  // Enable pullups
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
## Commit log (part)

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2025-07-04 docs update
2025-07-10 claude fixes for FET_EN and CANMOBSet
    ● I've fixed the CAN interrupt corruption issue. The problem was a classic race condition:
    Root Causes:
    1. No interrupt protection in CANMOBSet - The function that configures MOBs and writes data wasn't atomic
    2. ISR re-enabled global interrupts with sei(), allowing nested interrupts
    3. CANPAGE register corruption - When RX interrupt fired during TX setup, it changed CANPAGE, causing remaining
    TX data to be written to wrong location
2025-07-11 in-progress update
2025-07-28 added claude context
2025-07-30 Add private context access info to CLAUDE.md
    Added paths to private context, machine info, and GitHub PAT location
    for easier access in future sessions.
2025-07-30 fixed announcement and status message race conditions
2025-08-06 ignore sync files
2025-08-06 Remove sync.ffs_db from tracking - machine-specific file
2025-09-06 WIP: Debugging CAN receive callback issues
    Current status:
    - CAN receive callback never gets called (breakpoint not triggered)
    - Module times out after 11.1s and announces itself
    - Pack Emulator successfully transmits heartbeat (0x517) every 200ms
    - Module does NOT receive these heartbeats, causing timeout/re-registration cycle
    Investigation findings:
2025-09-08 Fix cell string power initialization on power-on reset
    - Move sg_eStringPowerState to .noinit section to survive watchdog resets
    - Add explicit initialization to ESTRING_INIT on power-on reset
    - Cell string power state machine now properly starts and transitions
    - Verified cell processing is enabled (FAKE_CELL_DATA commented out)
2025-09-09 Add debug output for MODULE_DETAIL_REQUEST handling
    Added comprehensive debug logging to understand why module isn't sending MODULE_DETAIL responses:
    1. Log incoming detail requests with module ID, cell ID, and counts
    2. Log when scheduling cell detail response
    3. Log reasons for not scheduling (already sending, out of range)
    4. Log when attempting to send cell details
    5. Log when cell ID exceeds available cells
2025-09-09 Fix build errors - remove all debug statements
    Fixed compilation errors by removing all debug statements:
    - ModuleCPU does not have debug output functions (no DebugOut, DebugOutUint8, etc.)
    - Removed all debug statements added in previous commit
    - Kept the fix for sending MODULE_DETAIL for all requested cells
    - Added note to CLAUDE.md about no debug output capability
    The module now properly:
2025-09-09 Enable FAKE_CELL_DATA for testing MODULE_DETAIL responses
    Added #define FAKE_CELL_DATA to use simulated cell data for testing.
    When FAKE_CELL_DATA is defined:
    - Module uses hardcoded test data for 16 cells
    - Cell voltages range from 3.4-3.9V
    - Cell temperatures range from 21-27°C
    - sg_u8CellCPUCount will be set to 16 (64 bytes / 4 bytes per cell)
2025-09-09 Debug: Send raw StringData values in MODULE_DETAIL when converted values are zero
    - When CellDataConvert returns 0 voltage but stats show valid data
    - Send raw voltage value in temperature field
    - Send raw temperature value in voltage field
    - This helps diagnose why StringData appears empty despite valid stats
2025-09-09 Fix MODULE_DETAIL to use raw StringData values directly
    - Remove unnecessary CellDataConvert() call that was returning zeros
    - Use raw values directly from StringData like CalculateStats() does
    - Clear MSG_CELL_DISCHARGE_ACTIVE bit from voltage if present
    - This fixes the issue where MODULE_DETAIL returned zeros despite valid stats
2025-09-09 Fix: Preserve StringData across frames for MODULE_DETAIL responses
    - Don't clear StringData in FrameInit(false) partial initialization
    - StringData contains the last received cell data and must persist
    - This allows MODULE_DETAIL to return actual cell values between frames
    - Min/max/avg stats already persist, now individual cell data does too
2025-09-09 Fix MODULE_DETAIL to properly convert voltage and temperature
    - Use CellDataConvertVoltage() to convert raw voltage to millivolts
    - Use CellDataConvertTemperature() to convert raw temperature
    - These conversion functions handle scaling and validation
    - Matches the conversion done in CalculateStats() for min/max/avg
2025-09-10 Fix sg_u8CellCPUCountMost initialization issue
    - Explicitly initialize sg_u8CellCPUCountMost to 0 after memset in full init
    - Fixes issue where max cells was reporting 170 (0xAA) instead of actual count
    - Note: 29.25V voltage issue was hardware-related (resistor config for 48V)
2025-09-12 WIP: Move VUART diagnostic sync signal from PC7 to PD7
    - PC7 drives flipflop clock on REV E+ boards, causing conflicts
    - Moved profiler output to PD7 which is unused
    - Signal not appearing on PD7 despite code executing (needs hardware debugging)
2025-09-12 WIP: VUART edge correction and cell detail fixes
    - Implemented edge-triggered timing correction for VUART RX
    - Moved diagnostic sync signal from PC7 to PD5
    - Fixed cell detail target calculation (was same, now +1)
    - Removed unsolicited status messages during cell processing
    - Edge correction made VUART less reliable, needs investigation
    - Cell detail sequence still erratic despite fixes
2025-09-14 Add missing noinit variable initializations on power-on reset
    - Initialize all critical status message flags to false
    - Initialize safety flags (overcurrent, discharge, balance) to false
    - Initialize SOC, SOH, cell status variables to 0
    - Initialize cell count mismatch tracking variables
    - Set sg_bSendAnnouncement to true for startup announcement
    - Ensures clean startup state for all control variables
2025-09-17 Fix CAN reliability issues in ModuleCPU
    - Fixed hardware detail flag to clear regardless of CAN send success
    Hardware detail is not critical, so don't retry forever if CAN is busy
    - Fixed critical race condition bug in CAN interrupt handler
    Commented out incorrect sg_bBusy/sg_bInRetransmit clearing in RX MOB context
    These flags should only be cleared in TX MOB context to prevent overlapping TX operations
    This was causing module lockups and CAN peripheral confusion
2025-09-17 Add comprehensive CAN MOB interrupt flow documentation
    - Documents normal TX flow and how TX MOB gets re-enabled via CANMOBSet
    - Documents TX error/retry flow
    - Documents normal RX flow and continuous re-enabling
    - Explains why system works: CANMOBSet always re-enables on next TX
    - Notes potential issue: TX MOB stays disabled after last transmission
    - Helps future debugging by clarifying the non-obvious re-enable mechanism
2025-09-17 Update context with September 17 CAN reliability fixes
2025-09-22 Fix CAN TX stuck busy issue with timeout mechanism
    - Changed sg_bBusy from bool to uint8_t timeout counter
    - Added CANCheckTxStatus() to poll TXOK and recover from stuck TX
    - Timeout after 200ms (2 ticks) if TX doesn't complete
    - Called every 100ms from main loop as backup to interrupts
    - Prevents permanent CAN lockups when interrupts fail
2025-09-22 Improve CAN TX timeout mechanism and add diagnostics
    - Fixed timeout extension on retransmits (don't reset on AERG)
    - Added diagnostic counters for timeouts, errors, and polled TXOK
    - Properly disable TX MOB interrupt on timeout
    - Clear sg_bInRetransmit flag on timeout/error recovery
    - Export diagnostic functions to monitor CAN health
2025-09-22 Add bus-off recovery delay and error counter diagnostics
    Problem: Module rapidly cycling in/out of bus-off state
    Root cause: Immediate retransmission after bus-off causing re-entry
    Changes:
    - Add 1-second delay after bus-off before allowing transmissions
    - Track error counter changes to detect rapid accumulation
    - Add CANGetTEC()/CANGetREC() for error counter monitoring
2025-09-23 refactor: use shared VUART timing constants from Shared.h
    - Replaced local VUART_BIT_TICK_OFFSET (was 7) with VUART_ISR_OVERHEAD from Shared.h
    - Now uses VUART_SAMPLE_OFFSET for start bit sampling
    - Set to 0 for nominal timing experiments
    - Ensures consistent timing with CellCPU
2025-09-23 feat: make edge sync configurable with #ifdef ENABLE_EDGE_SYNC
    - Edge sync is now disabled by default (commented out)
    - Can be easily enabled for experiments by uncommenting the define
    - Fixed sync formula to use VUART_SAMPLE_OFFSET for consistency
    - Properly handles interrupt enable/disable based on mode
    - Wrapped all edge sync code in conditional compilation blocks
    This allows easy A/B testing between fixed timing and edge sync modes.
2025-09-24 Document MODULE_DETAIL protocol change
    - Byte 1 now reports actual cells received vs expected count
    - Added cell ordering and mapping documentation
    - Explained VUART reverse-order chain architecture
2025-09-25 Replace EEPROM-based string tolerance with compile-time constant and fix VUART timeout detection
    - Replaced sg_u8SequentailCountMismatchThreshold EEPROM variable with SEQUENTIAL_COUNT_MISMATCH_THRESHOLD #define (set to 5)
    - Fixed CellStringProcess() to handle zero bytes received as communication failure
    - Now properly detects complete VUART communication failures (no interrupts)
    - Zero cells received triggers mismatch counter, leading to automatic string reset after threshold
    - Pack controller receives accurate cell count (0) to mark data as stale
2025-09-26 Add end of charge voltage calculation to hardware detail message
    - Calculate as cellsExpected * 4.2V * 0.95
    - Encode in 15mV increments to match module voltage reporting
    - Value reported in bytes 4-5 of hardware detail CAN message
2025-09-28 Refactor frame structure: separate FrameMetadata from cell buffer
    - Created FrameMetadata structure containing all control/status fields
    - Updated FrameData to use metadata 'm' field and flexible buffer 'c'
    - Changed all sg_sFrame.xxx references to sg_sFrame.m.xxx throughout codebase
    - Added nstrings field for tracking multiple string readings in buffer
    - Ensures frame size is exactly 1024 bytes (2 sectors)
2025-09-28 Implement circular buffer for multiple string readings
    - Added invalid cell markers (0xFFFF/0x7FFF) for non-reporting cells
    - Dynamic buffer sizing: 11 readings for 20 cells, 4 for 50, 2 for 94
    - Initialize buffer with invalid markers at READ frame start
    - Always advance buffer at WRITE frame (never gets stuck)
    - CAN responses use GetLatestCompleteString() for consistent data
    - Frame counter increments with each reading
2025-09-28 Clean up git tracking - exclude build artifacts
    - Updated .gitignore to exclude all build files
    - Keep only .elf and .hex executables
    - Remove .o, .d, .map, .lss, .eep files from tracking
    - Remove Atmel Studio temp files (.atsuo, componentinfo.xml)
    - Remove backup files from tracking
    - Reduces repo size and avoids unnecessary merge conflicts
2025-09-29 Add EEPROM tools and GUI editor
    - Add geneeprom CLI tool for creating .eep files
    - Create Windows Forms GUI editor for EEPROM files
    - Visual editing of metadata fields (unique ID, cell count, currents)
    - Frame counter buffer visualization with wear leveling tracking
    - Proper encoding/decoding using CURRENT_FLOOR offset (-655.36A)
    - Fix count mismatch field (1 byte, not 2 bytes)
2025-10-02 Fix build error - comment out DebugOut using undefined u8RegID
2025-10-19 added hardware reference

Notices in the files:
main.c:
(C) Copyright 2023-2024 Modular Battery Technologies, Inc.
hardware-reference/module-controller-avr/module controller.kicad_pcb:
(C)2024 modbatt
